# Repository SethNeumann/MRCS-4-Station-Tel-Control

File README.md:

# REPO NAME: MRCS-4-Station-Tel-Control

## License: Creative Commons Attribution-NonCommercial-ShareAlike

MRCS-4-Station-Tel-Control panel.  

Developed for Chris Czyzewski, 4 of the stations and the DS need to be able to signal 4 stations.  Each has a "Start" push button and a LED to indicate
"Call Pending."  An optional second set of LEDs will show station status (off hook) but Chris isn't using it.  This board will work with a dedicated
distribution board to power them and allow routing of signals among the stations.

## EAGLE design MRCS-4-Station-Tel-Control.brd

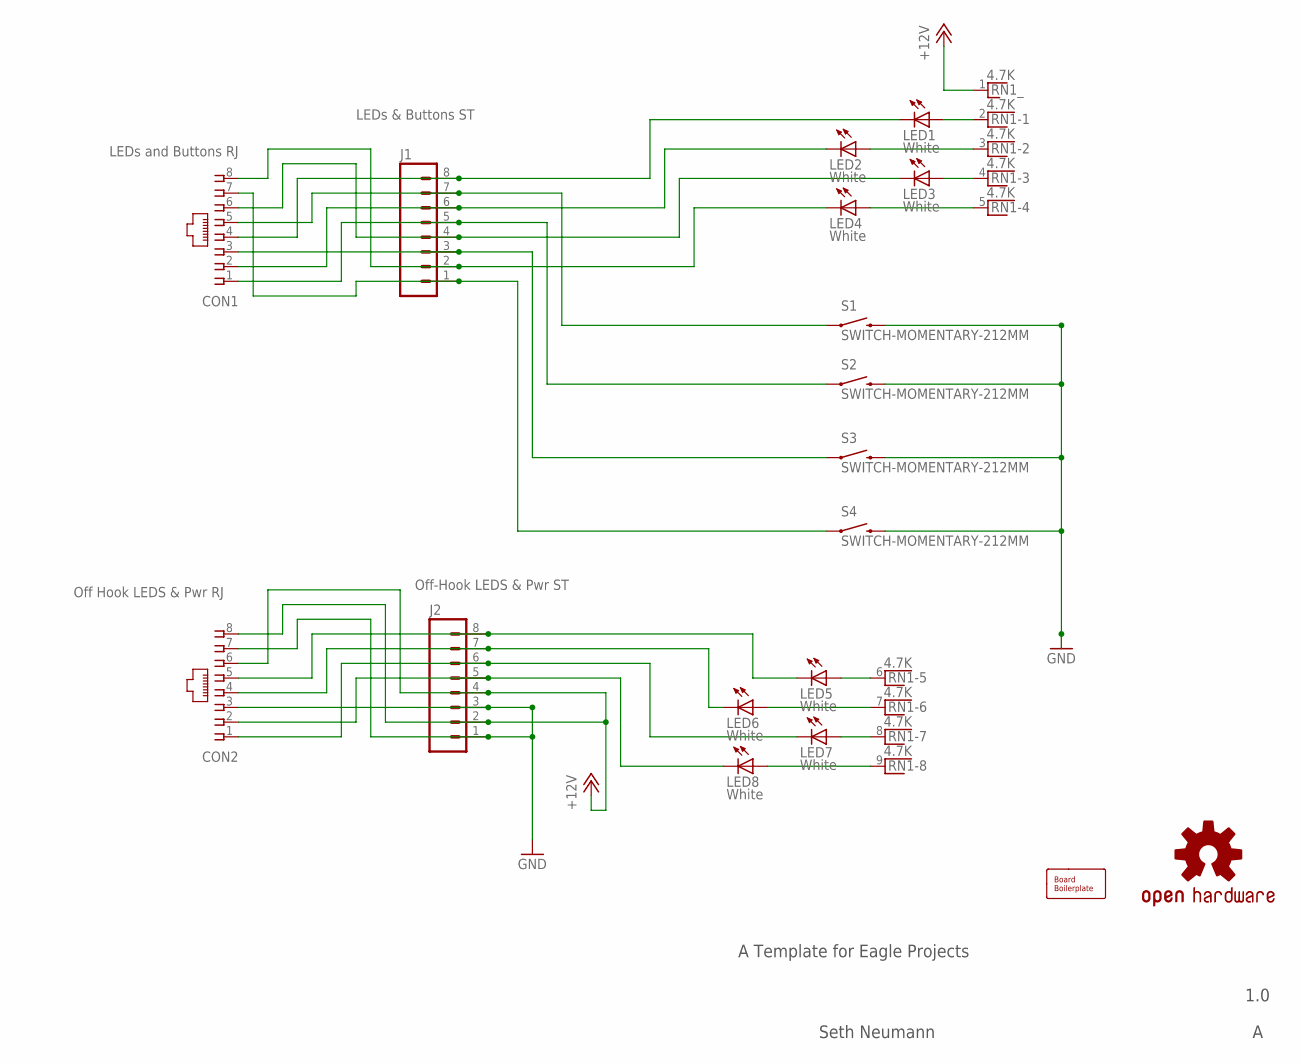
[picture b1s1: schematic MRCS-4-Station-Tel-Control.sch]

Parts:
BOARD1: BOARD80X100; BOARD-DINRAIL-3.17INX10CM
CON1: LEDs and Buttons RJ; RJ45-NO-SHIELD
CON2: Off Hook LEDS & Pwr RJ; RJ45-NO-SHIELD
J1: LEDs & Buttons ST; 1X08_LOCK
J2: Off-Hook LEDS & Pwr ST; 1X08_LOCK
LED1, LED2, LED3, LED4, LED5, LED6, LED7, LED8: White; LED5MM
OSHW1: DOC-OSHW-LOGO-M; OSHW-LOGO-M
RN1: 4.7K; RN-9
S1, S2, S3, S4: SWITCH-MOMENTARY-212MM; TACTILE-PTH-12MM

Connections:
+12V: CON2.6, CON2.8, J2.2, J2.4, RN1.1
GND: CON2.3, CON2.7, J2.1, J2.3, S1.3 (2), S2.3 (2), S3.3 (2), S4.3 (2)
unnamed: LED1.A, RN1.2
unnamed: LED2.A, RN1.3
unnamed: LED3.A, RN1.4
unnamed: LED4.A, RN1.5
unnamed: LED5.A, RN1.6
unnamed: LED6.A, RN1.7
unnamed: LED7.A, RN1.8
unnamed: LED8.A, RN1.9
unnamed: CON1.4, J1.8, LED1.K (C)
unnamed: CON1.1, J1.5, S2.1
unnamed: CON1.5, J1.7, S1.1
unnamed: CON1.3, J1.3, S3.1
unnamed: CON1.6, J1.4, LED3.K (C)
unnamed: CON1.7, J1.1, S4.1
unnamed: CON1.8, J1.2, LED4.K (C)
unnamed: CON1.2, J1.6, LED2.K (C)
unnamed: CON2.5, J2.8, LED5.K (C)
unnamed: CON2.4, J2.7, LED6.K (C)
unnamed: CON2.1, J2.6, LED7.K (C)
unnamed: CON2.2, J2.5, LED8.K (C)

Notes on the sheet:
A Template for Eagle Projects
1.0
Seth Neumann

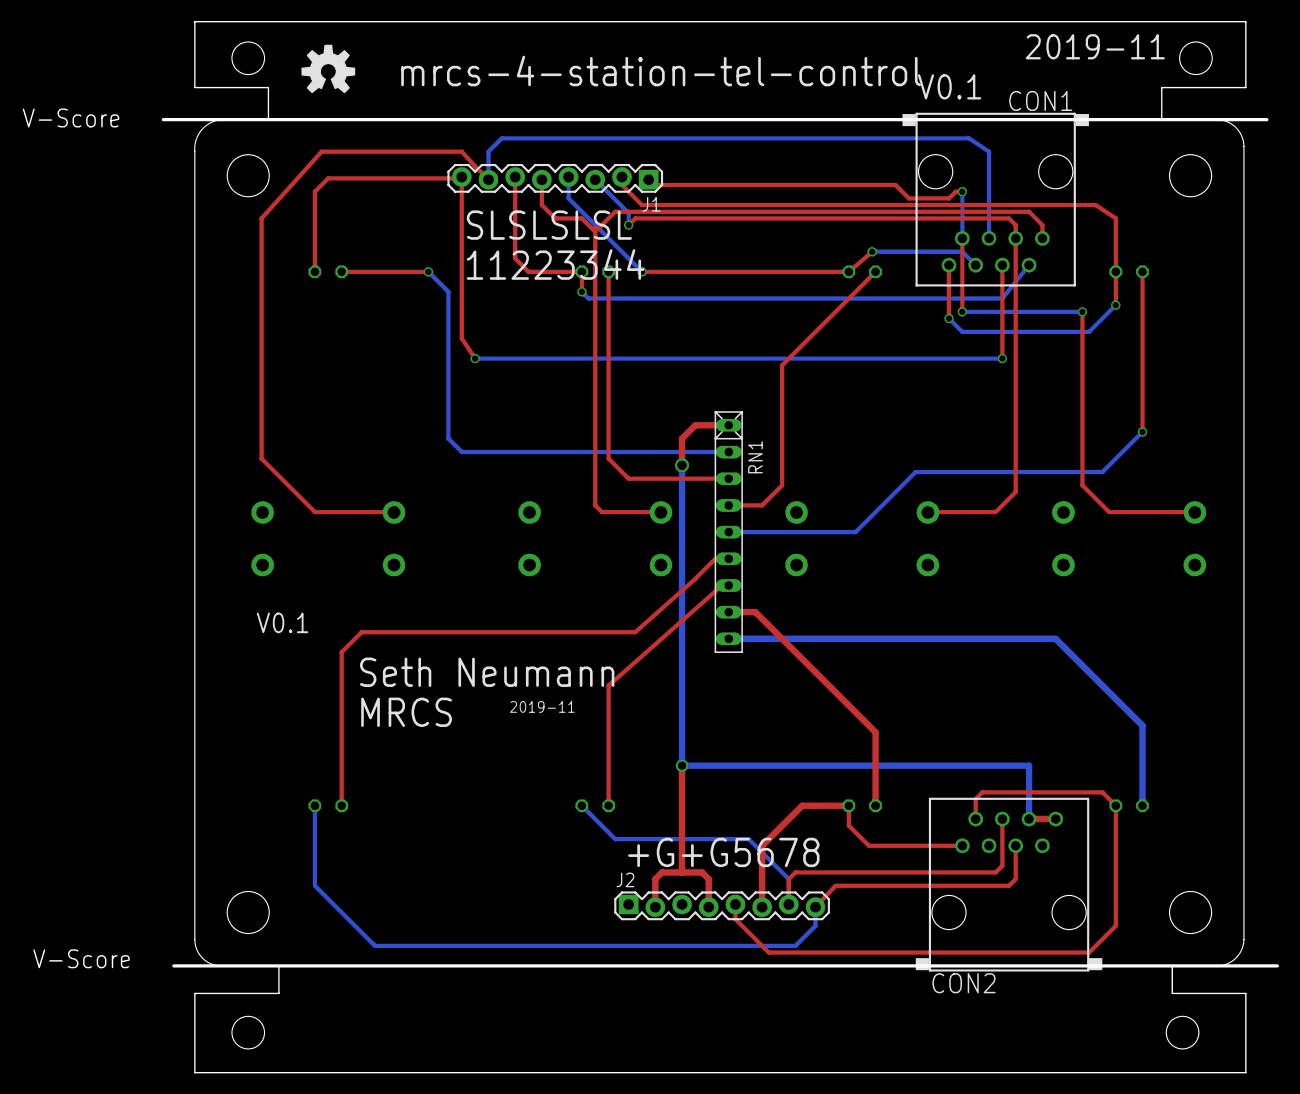
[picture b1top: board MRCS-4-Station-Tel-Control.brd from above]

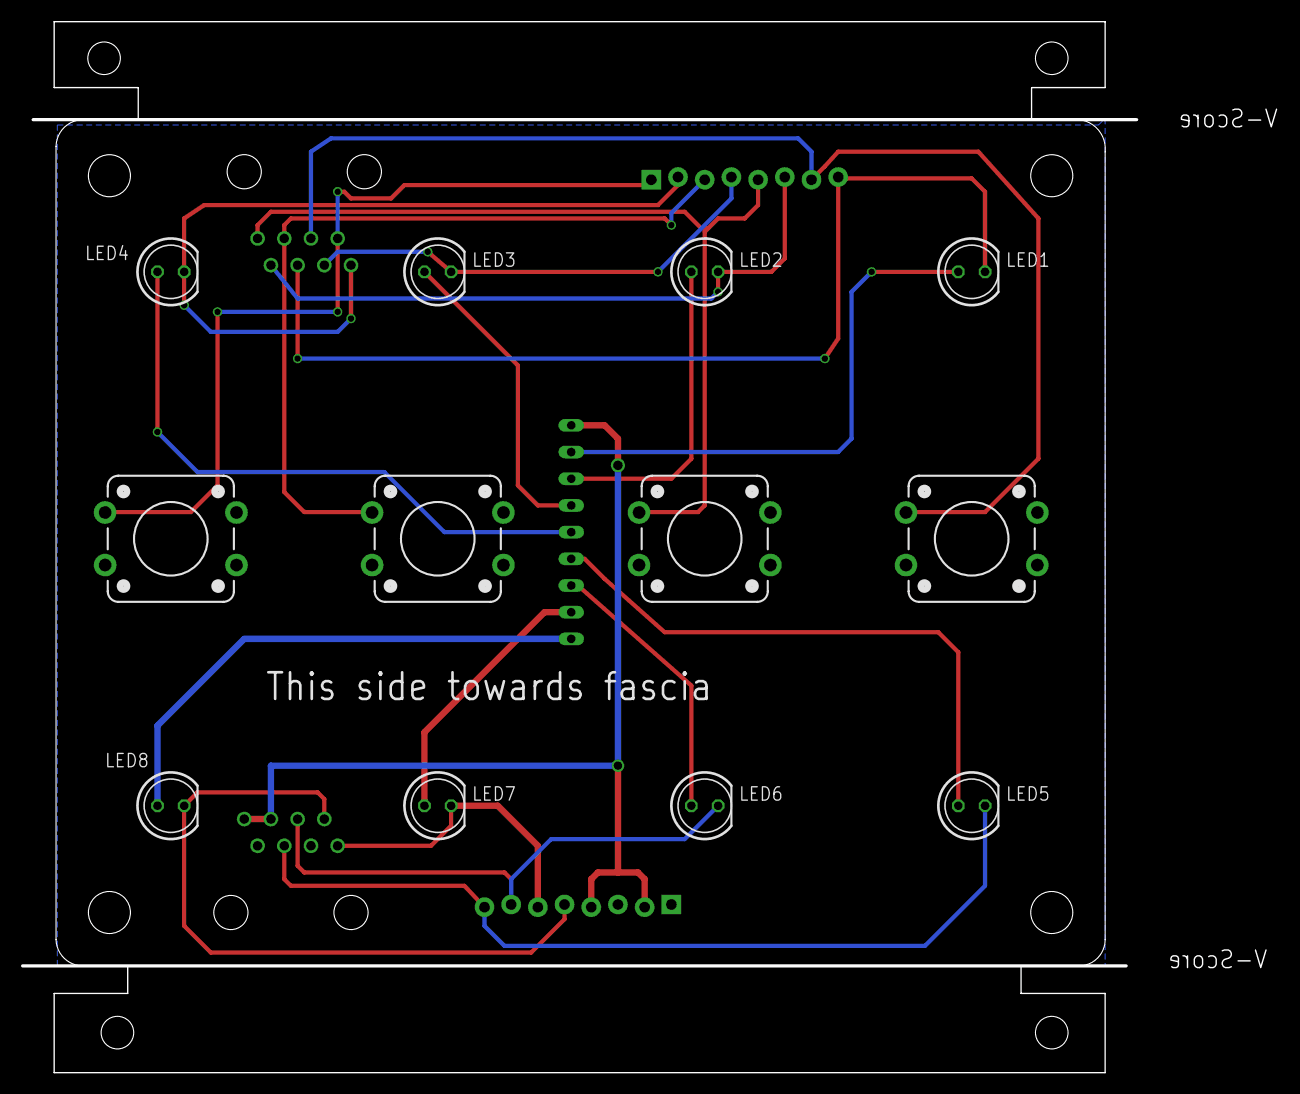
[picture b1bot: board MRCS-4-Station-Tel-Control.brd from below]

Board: 2 copper layers, 106.0 x 100.0 mm, 22 parts (12 on the bottom side), 22 nets.

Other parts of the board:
U$1: MRCSLOGOTOP
U$2: CA-PROP65WARNING
U$3: MRCSLOGOBTM

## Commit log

2021-08-09 initial commit
    set the project up
2021-08-09 initial commit of sch and brd
    renamed templates to conform
2021-08-10 First pass of board complete
    This is the first iteration of the board.
2021-08-10 clean up git directory
    moved files around to keep things neat
2021-08-14 Moved labels for push buttons and LEDs to back
    A learning exercise involving mirror, rotate and a lot of moving traces from top to bottom and vice versa

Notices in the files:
parts and their libraries:
SparkFun-Electromechanical: Licensing: CC v3.0 Share-Alike You are welcome to use this library for commercial purposes.
SPCoast: http://freedomdefined.org/OSHW Creative Commons - Attribution - ShareAlike 3.0
